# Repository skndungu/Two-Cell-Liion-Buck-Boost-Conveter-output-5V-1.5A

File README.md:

# Two-Cell-Liion-Buck-Boost-Conveter-output-5V-1.5A
Power bank based on two Liion cells to charge your phone at 5V 1.5A , depending on battery capacity it could last as your capacity allows

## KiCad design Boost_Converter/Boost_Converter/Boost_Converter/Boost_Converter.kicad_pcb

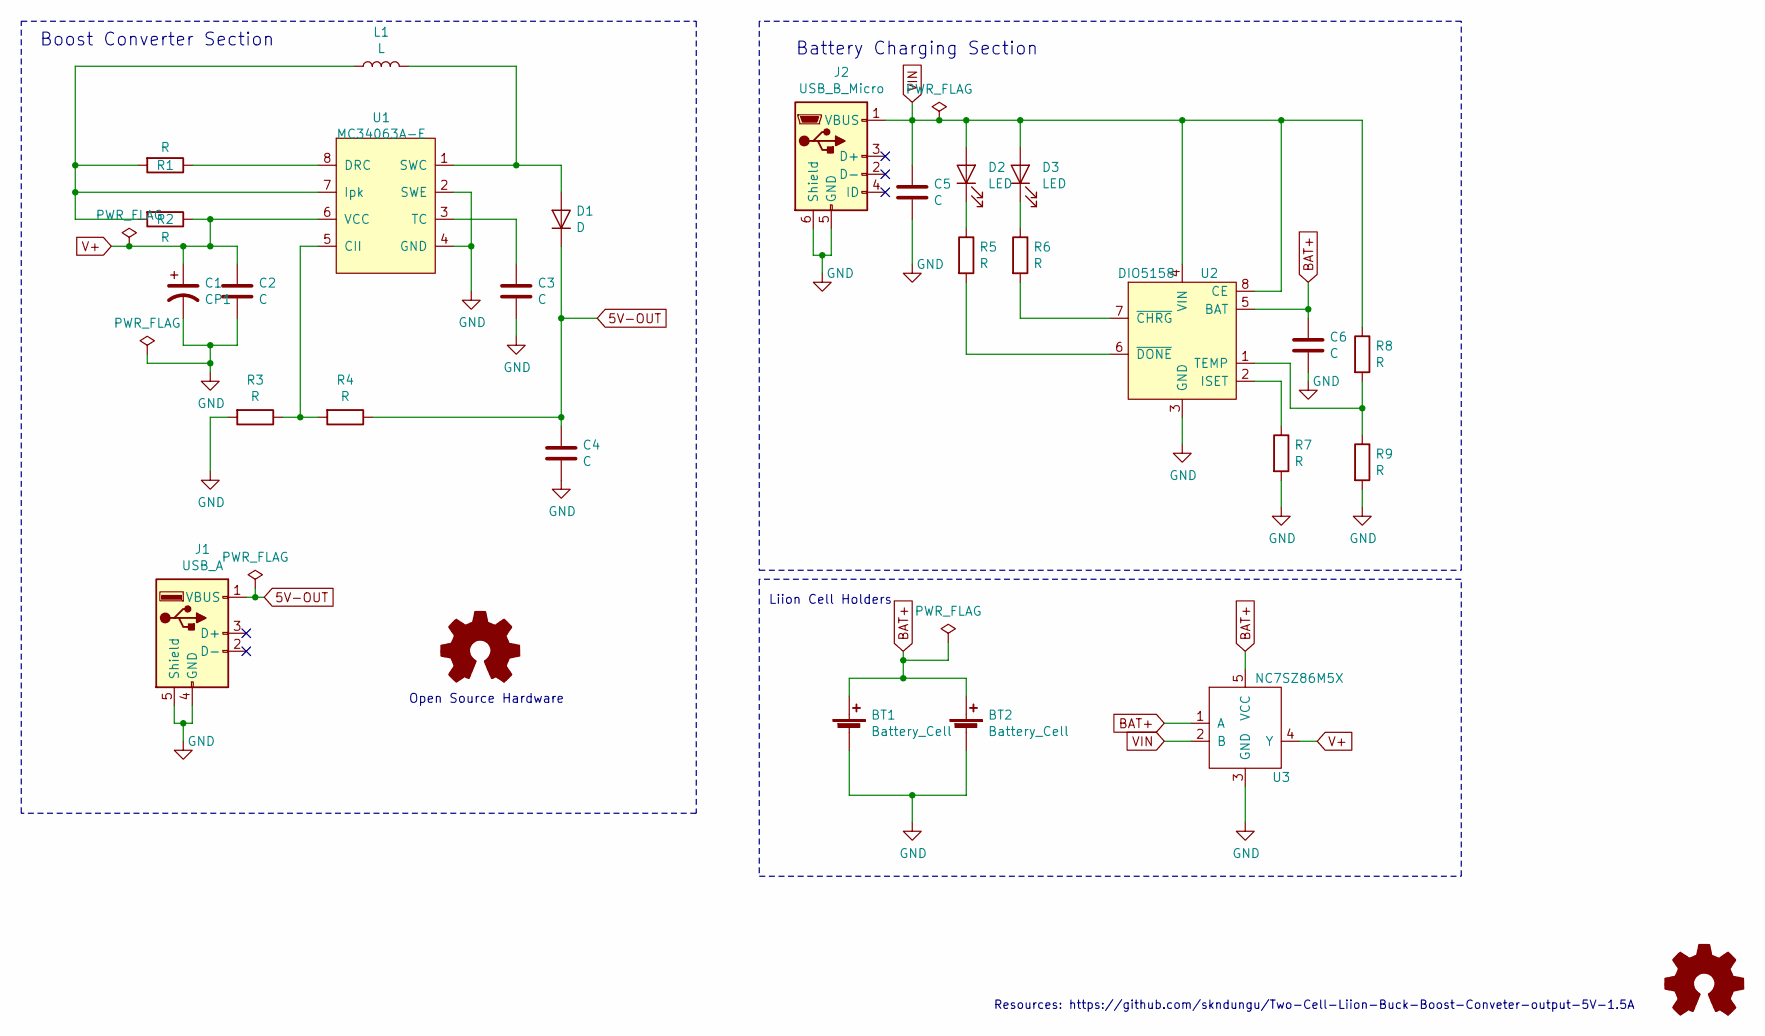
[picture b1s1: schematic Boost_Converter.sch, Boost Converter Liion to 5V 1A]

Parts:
BT1, BT2: Battery_Cell; 18650-HOLDER
C1: CP1; CP_Elec_5x4.5
C2, C3, C4, C5, C6: C; C_1206_3216Metric_Pad1.42x1.75mm_HandSolder
D1: D; D_SOD-323_HandSoldering
D2, D3: LED; LED_1206_3216Metric_Castellated
J1: USB_A; PRT-09011
J2: USB_B_Micro; USB_Micro-B_Molex-105017-0001
L1: L; L_Bourns_SRR1260
R1, R2, R3, R4, R5, R6, R7, R8, R9: R; R_1206_3216Metric
U1: MC34063A-E; SOIC-8
U2: DIO5158; SOIC-8
U3: NC7SZ86M5X

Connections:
5V-OUT: C4.1, D1.1 (K), J1.1 (VBUS), R4.1
BAT+: BT1.1 (+), BT2.1 (+), C6.1, U2.5 (BAT), U3.1 (A), U3.5 (VCC)
GND: BT1.2 (-), BT2.2 (-), C1.2, C2.2, C3.2, C4.2, C5.2, C6.2, J1.4 (GND), J1.5 (Shield), J2.5 (GND), J2.6 (Shield), R3.2, R7.2, R9.2, U1.2 (SWE), U1.4 (GND), U2.3 (GND), U3.3 (GND)
unnamed: C3.1, U1.3 (TC)
unnamed: D1.2 (A), L1.2, U1.1 (SWC)
unnamed: D2.1 (K), R5.1
unnamed: D3.1 (K), R6.1
unnamed: L1.1, R1.2, R2.2, U1.7 (Ipk)
unnamed: R1.1, U1.8 (DRC)
unnamed: R3.1, R4.2, U1.5 (CII)
unnamed: R5.2, U2.6 (~DONE)
unnamed: R6.2, U2.7 (~CHRG)
unnamed: R7.1, U2.2 (ISET)
unnamed: R8.2, R9.1, U2.1 (TEMP)
V+: C1.1, C2.1, R2.1, U1.6 (VCC), U3.4 (Y)
VIN: C5.1, D2.2 (A), D3.2 (A), J2.1 (VBUS), R8.1, U2.4 (VIN), U2.8 (CE), U3.2 (B)

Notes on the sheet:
Boost Converter Section
Battery Charging Section
Liion Cell Holders
Resources: https://github.com/skndungu/Two-Cell-Liion-Buck-Boost-Conveter-output-5V-1.5A
Open Source Hardware

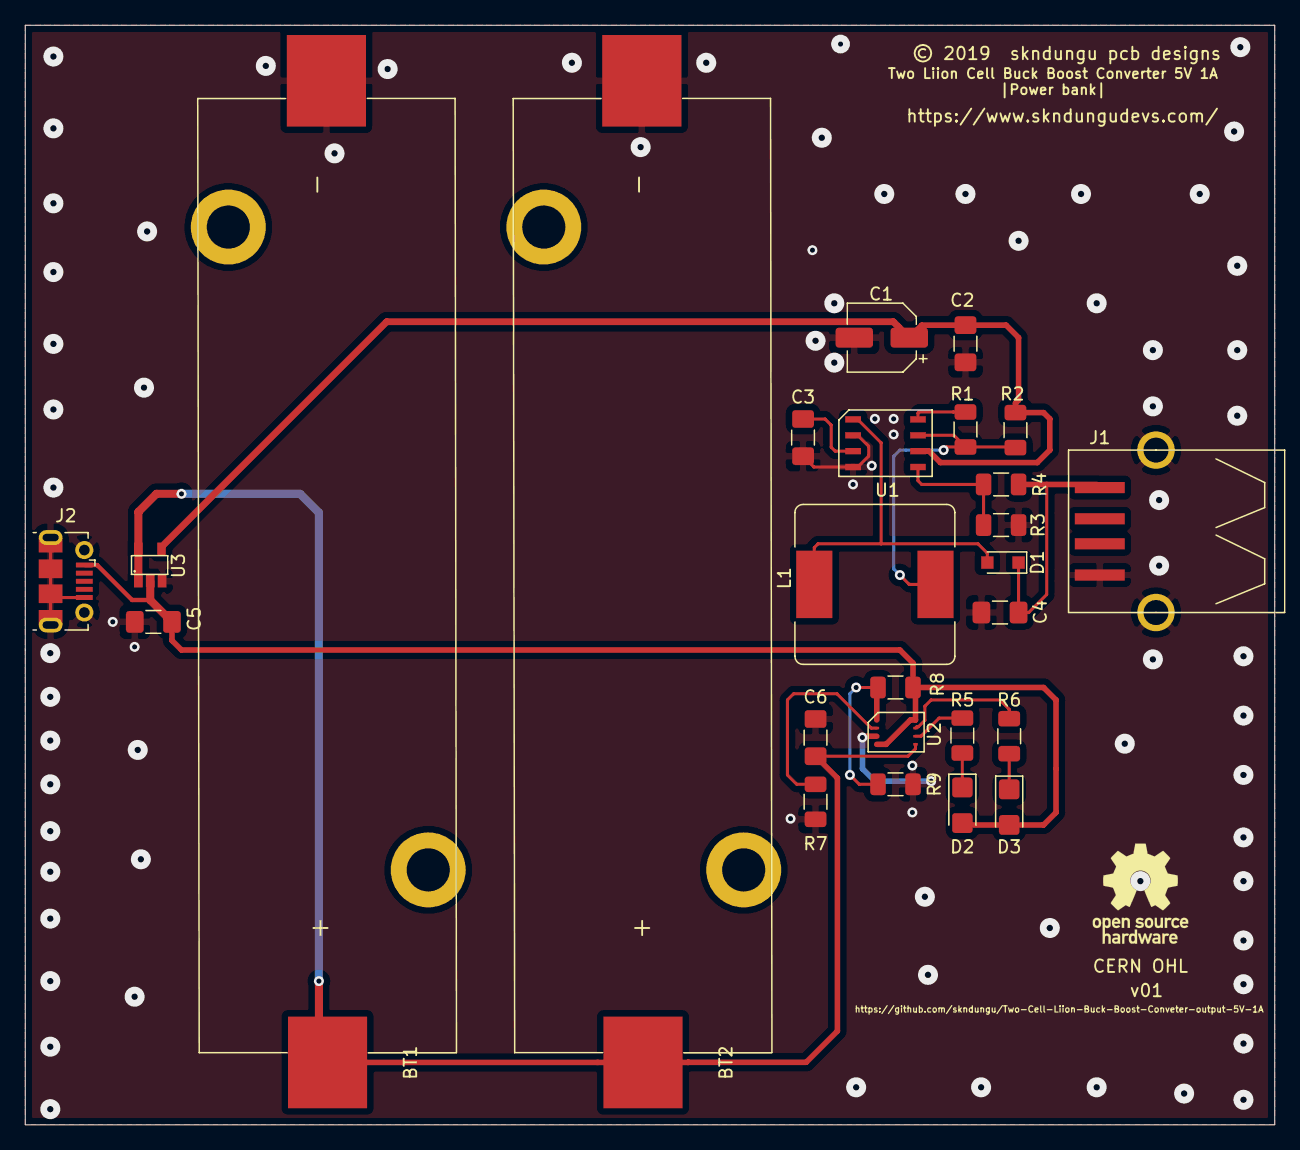
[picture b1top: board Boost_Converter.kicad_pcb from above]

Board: 2 copper layers, 100.0 x 88.0 mm, 26 parts (0 on the bottom side), 16 nets.

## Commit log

2019-08-06 Add files via upload
    FInal update files

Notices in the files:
Boost_Converter/Boost_Converter/Boost_Converter/Boost_Converter.kicad_pcb:
© 2019
CERN OHL
Boost_Converter/Boost_Converter/Boost_Converter/Boost_Converter.sch:
Licence: CERN OHL
